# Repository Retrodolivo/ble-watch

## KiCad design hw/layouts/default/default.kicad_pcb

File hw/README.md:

# Watch hardware (atopile)

Schematic-as-code for the BLE binary watch, written in [atopile](https://atopile.io) `.ato`.
Status: **first draft**. It compiles and produces a KiCad PCB with all 76 parts and nets
(nothing placed or routed yet). Every value marked VERIFY must be checked before ordering.

## Build

```bash
uv tool install --python 3.14 "atopile==0.15.8"   # 0.12.x is retired; 0.16+ is the web app
cd hardware/watch-hw            # wherever you put this folder
ato build                       # -> layouts/default/default.kicad_pcb, build/builds/default/*
```

Open `layouts/default/default.kicad_pcb` in KiCad 9 to see the parts and the ratsnest.
atopile is code-first: there is no drawn schematic sheet. The `.ato` files *are* the schematic.

## Files

| File | What it describes |
|------|-------------------|
| `main.ato` | Top level `Watch`: wires the blocks together, GPIO map |
| `power.ato` | Pogo pads, TVS + Schottky, nPM1100 charger/buck (3.0 V), battery pads |
| `mcu.ato` | nRF52840 aQFN73, decoupling, DC/DC, 32 MHz + 32.768 kHz crystals, RF match, chip antenna, Tag-Connect SWD |
| `accel.ato` | LIS2DW12 on I2C (0x18) with INT1/INT2 and pull-ups |
| `display.ato` | 11 yellow LEDs (5 hours, 6 minutes), each GPIO -> 1 k -> LED -> GND |
| `status.ato` | Red + green heartbeat LEDs (GPIO -> 10 k -> LED -> GND), VBAT divider (1 M + 1 M, 100 nF) to AIN1 |
| `parts/` | One folder per physical part: `.ato` + KiCad footprint + symbol |
| `tools/genparts.py` | Script that generated `parts/` from the official KiCad libraries |

## GPIO map

Every signal that also exists on the DK uses the same nRF pin as the DK breadboard
(`app/boards/nrf52840dk_nrf52840.overlay`). Only INT2, CHG, ERR and ship mode are watch-only.

| Function | nRF52840 pin |
|----------|--------------|
| Hours 16, 8, 4, 2, 1 | P1.04, P1.05, P1.06, P1.07, P1.08 |
| Minutes 32, 16, 8, 4, 2, 1 | P1.10, P1.11, P1.12, P1.13, P1.14, P1.15 |
| I2C SDA / SCL | P0.26 / P0.27 |
| Accel INT1 / INT2 | P1.03 / P0.12 |
| Charger CHG / ERR (open drain, use internal pull-up) | P0.11 / P1.09 |
| Ship mode (output) | P0.15 |
| Status LED green / red (active high) | P0.13 / P0.14 |
| Battery sense (VBAT / 2) | P0.03 = AIN1 |
| 32.768 kHz crystal | P0.00 / P0.01 |
| SWD + reset | SWDIO, SWDCLK, P0.18 |

## Parts and LCSC numbers

Every part is a fixed manufacturer part number with its own local footprint, and every part that gets
assembled has an LCSC number (`supplier_partno` in `parts/*/*.ato`). `ato build` writes a complete
JLCPCB BOM to `build/builds/default/default.bom.csv` (28 lines, 71 parts). The 4 pogo/battery pads and
the Tag-Connect footprint are bare copper with no part, so their LCSC number is `none` and the JLC BOM
leaves them out. The build prints 5 "Non-LCSC parts" warnings for them; these are expected.

We don't use atopile's cloud picker or `ato create part`. Both depend on atopile's components API,
which returned HTTP 502 on 2026-11-18 (atopile 0.15.8 is the last CLI release and is in maintenance mode).
Fixed parts also keep the BOM deterministic.

Three parts differ from Nordic's reference Murata parts, which LCSC doesn't stock. Same size and value:

| Part | Reference part | Used (LCSC) | Check before ordering |
|------|-----|-----------|-----------------------|
| `C_12pF_0402` | GRM1555C1H120JA01D | GJM1555C1H120GB01D (C161305) | High-Q GJM series, ±2 %. Drop-in |
| `L_3n9H_0402` | LQP15MN3N9B02D (obsolete) | LQG15HH3N9B02D (C907911) | Multilayer, not thin-film: RF match may need retuning |
| `L_10uH_0603` | LQM18PN100MFRL | LQM18DZ100M70L (C3911082) | Check rated current and DCR for the nRF52840 DC/DC |

When you change a part, update its `supplier_partno` and the matching row in `tools/genparts.py`, so
regenerating `parts/` keeps the number. LCSC numbers were looked up on 2026-11-18. Check stock and
lifecycle before ordering: several of the Murata MLCCs are marked NRND by other distributors.

## Open questions (decide before layout)

1. **nPM1100 QFN pinout and exposed-pad size** come from LCSC/Flux data, not Nordic's own QFN spec. Verify, and pick the
   matching footprint (currently `QFN-24-1EP_4x4mm_P0.5mm_EP2.6x2.6mm`). The WLCSP version is smaller but harder to assemble.
2. **Ship mode without buttons.** Firmware can drive SHPACT to enter ship mode (for storage); plugging the charger wakes it.
   SHPHLD is left unconnected. Check that it has an internal pull-up, or tie it high.
3. **nRF52840 passive values** (DEC1/3/4/6, DECUSB, VDD caps, the 10 uH + 15 nH DC/DC pair, 12 pF load caps) follow
   Nordic's reference circuit from memory. Check them against the nRF52840 PS "Reference circuitry" (aQFN73, DC/DC enabled).
4. **Antenna tuning.** Nordic's 3.9 nH / 0.8 pF filter is followed by a pi network (0 R + two DNP shunts) for tuning the
   2450AT18A100 on the real board with a VNA. Keep the antenna in a corner with the ground clearance from Johanson's layout.
5. **Charge-pad protection.** The pads see only 5 V in, through a 6 V bidirectional TVS and a series Schottky (RB521S30),
   which also blocks a reversed cable. The Schottky drops ~0.4 V, which leaves ~4.6 V at VBUS. The TVS footprint
   is a generic 0402 and must be checked against TI's DPY land pattern.
6. **Charge current** is 100 mA (ICHG = 4.7 k, about 0.66 C for 150 mAh). Check the cell's maximum charge rate.
7. **Battery level.** An always-on VBAT divider (1 M + 1 M, 2.1 uA) goes to P0.03/AIN1, the same SAADC input the
   firmware uses on the DK. A switched divider (a FET to cut the 2.1 uA)
   is possible but not worth it: the chip sleeps at a similar current. The 100 nF must stay close to the pin.
8. **LED brightness.** 1 mA through clear resin may be too bright or too dim. The resistors (1 k) are easy to change.
   The status LEDs run at ~0.12 mA (10 k); check that the flash is visible.

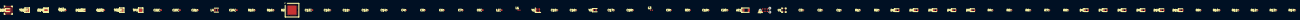
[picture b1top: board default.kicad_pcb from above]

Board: 2 copper layers, 76 parts (0 on the bottom side), 61 nets, no tracks yet.

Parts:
AE1: Johanson_2450AT18x100
C1, C2, C3, C4, C5, C6, C7, C9, C10, C11, C12, C14, C15, C16, C17, C18, C19, C20, C21, C26: C_0402_1005Metric
C8, C13, C22, C23, C24, C25: C_0603_1608Metric
D1, D2, D3, D4, D5, D6, D7, D8, D9, D10, D11, D14, D15: LED_0603_1608Metric
D12: D_SOD-523
D13: D_0402_1005Metric
J1: Tag-Connect_TC2030-IDC-NL_2x03_P1.27mm_Vertical
L1, L3: L_0402_1005Metric
L2: L_0603_1608Metric
L4: L_Murata_DFE201610P
R1, R2, R3, R4, R5, R6, R7, R8, R9, R10, R11, R12, R13, R14, R15, R16, R17, R18, R19, R20: R_0402_1005Metric
TP1, TP2, TP3, TP4: TestPoint_Pad_2.0x2.0mm
U1: LGA-12_2x2mm_P0.5mm
U2: Nordic_AQFN-73-1EP_7x7mm_P0.5mm
U3: QFN-24-1EP_4x4mm_P0.5mm_EP2.6x2.6mm
Y1: Crystal_SMD_2016-4Pin_2.0x1.6mm
Y2: Crystal_SMD_2012-2Pin_2.0x1.2mm

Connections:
1: AE1.1, C20.1, R3.2
2: D1.2, R4.2
ANT: L3.1, U2.H23
DCC: L2.1, U2.B3
DEC: C21.1, U3.21
DECUSB: C8.1, U2.AC5
ICHG: R15.1, U3.12
ISET: C25.1, U3.2, U3.3, U3.5, U3.9, U3.16
NRESET: J1.3, U2.AC13
NTC: R16.1, U3.14
SW: L4.1, U3.22
SWDCLK: J1.4, U2.AA24
SWDIO: J1.2, U2.AC24
battery-hv: C22.1, R18.1, TP3.1, U3.15
chg_n: U2.T2, U3.8
core-1: C4.1, U2.C1
core-1-1: C5.1, U2.D23
core-1-2: C6.1, L1.2, U2.B5
core-1-3: C7.1, U2.E24
core-1-4: C9.1, C19.1, L3.2, R3.1
core-1-5: C15.1, U2.B24, Y1.1
core-1-6: C16.1, U2.A23, Y1.3
core-1-7: C17.1, U2.D2, Y2.1
core-1-8: C18.1, U2.F2, Y2.2
core-1-9: L1.1, L2.2
err_n: U2.R1, U3.10
face-2: D2.2, R5.2
face-2-1: D3.2, R6.2
face-2-2: D4.2, R7.2
face-2-3: D5.2, R8.2
face-2-4: D6.2, R9.2
face-2-5: D7.2, R10.2
face-2-6: D8.2, R11.2
face-2-7: D9.2, R12.2
face-2-8: D10.2, R13.2
face-2-9: D11.2, R14.2
green: R19.1, U2.AD8
hour[0]: R4.1, U2.U24
hour[1]: R5.1, U2.T23
hour[2]: R6.1, U2.R24
hour[3]: R7.1, U2.P23
hour[4]: R8.1, U2.P2
hv: C1.1, C2.1, C3.1, C10.1, C11.1, C12.1, C13.1, C14.1, C24.1, J1.1, L4.2, R1.2, R2.2, U1.2, U1.9, U1.10, U2.A22, U2.AD14, U2.AD23, U2.B1, U2.W1, U2.Y2, U3.1
int1: U1.12, U2.V23
int2: U1.11, U2.U1
lv: C1.2, C2.2, C3.2, C4.2, C5.2, C6.2, C7.2, C8.2, C9.2, C10.2, C11.2, C12.2, C13.2, C14.2, C15.2, C16.2, C17.2, C18.2, C19.2, C20.2, C21.2, C22.2, C23.2, C24.2, C25.2, C26.2, D1.1, D2.1, D3.1, D4.1, D5.1, D6.1, D7.1, D8.1, D9.1, D10.1, D11.1, D13.2, D14.1, D15.1, J1.5, R15.2, R16.2, R17.2, TP2.1, TP4.1, U1.3, U1.6, U1.7, U1.8, U2.AD2, U2.B7, U2.EP, U2.F23, U3.4, U3.7, U3.19, U3.23, U3.25, Y1.2, Y1.4
minute[0]: R9.1, U2.A20
minute[1]: R10.1, U2.B19
minute[2]: R11.1, U2.B17
minute[3]: R12.1, U2.A16
minute[4]: R13.1, U2.B15
minute[5]: R14.1, U2.A14
power-1: D12.2, D13.1, TP1.1
red: R20.1, U2.AC9
scl: R1.1, U1.1, U2.H2
sda: R2.1, U1.4, U2.G1
sense: C26.1, R17.1, R18.2, U2.B13
ship_mode: U2.AD10, U3.6
status-2: D14.2, R19.2
status-2-1: D15.2, R20.2
vbus_protected: C23.1, D12.1, U3.17
